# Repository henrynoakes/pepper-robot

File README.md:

Contains a hosted place to work on the pcbs for my robot called pepper.

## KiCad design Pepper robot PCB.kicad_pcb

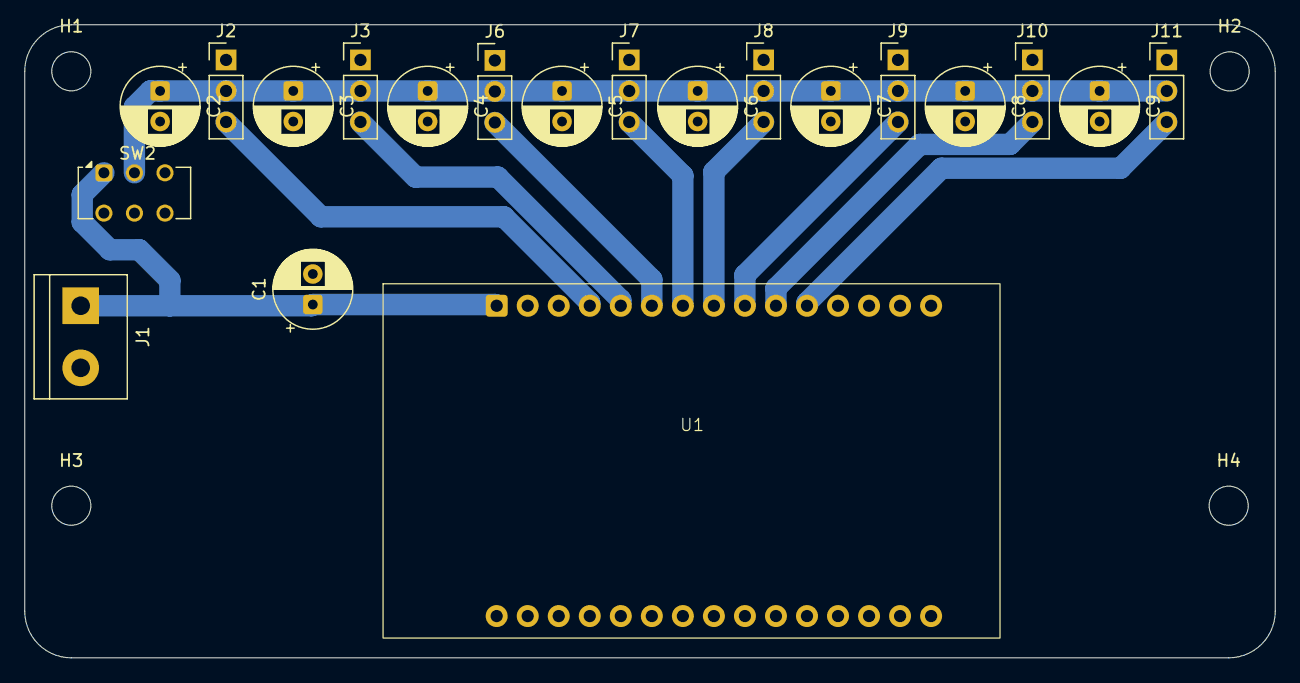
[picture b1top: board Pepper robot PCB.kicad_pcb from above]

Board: 2 copper layers, 102.4 x 51.8 mm, 24 parts (0 on the bottom side), 11 nets.

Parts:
C1: 100 μF; CP_Radial_D6.3mm_P2.50mm
C2, C3, C4, C5, C6, C7, C8, C9: 680 μF; CP_Radial_D6.3mm_P2.50mm
H1, H2, H3, H4: MountingHole; MountingHole_3.2mm_M3_ISO14580
J1: Terminal block; TerminalBlock_bornier-2_P5.08mm
J2, J3, J6, J7, J8, J9, J10, J11: Conn_01x03; PinHeader_1x03_P2.54mm_Vertical
SW2: SW_SPST; SW_CK_JS202011CQN_DPDT_Straight
U1: ESP32 DevKit 15x2; ESP32_DevKit_15x2_DIYMore

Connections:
+5V: C1.1, J1.1, SW2.1 (A), U1.1 (VIN)
GND: C1.2, C2.2, C3.2, C4.2, C5.2, C6.2, C7.2, C8.2, C9.2, J1.2, J2.1, J3.1, J6.1, J7.1, J8.1, J9.1, J10.1, J11.1, U1.2 (GND)
unnamed: J2.3, U1.4 (D12)
unnamed: J3.3, U1.5 (D14)
unnamed: J6.3, U1.6 (D27)
unnamed: J7.3, U1.7 (D26)
unnamed: J8.3, U1.8 (D25)
unnamed: J9.3, U1.9 (D33)
unnamed: C2.1, C3.1, C4.1, C5.1, C6.1, C7.1, C8.1, C9.1, J2.2, J3.2, J6.2, J7.2, J8.2, J9.2, J10.2, J11.2, SW2.2 (B)
unnamed: J10.3, U1.10 (D32)
unnamed: J11.3, U1.11 (D35)
